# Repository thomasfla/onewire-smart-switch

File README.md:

# onewire-smart-switch
Control and monitor any home lighting setup : a low cost 1-Wire module hidden in your walls.
Adapt to your existing switches, even to 3 and 4ways.

Open source and open hardware.

# details 
A full description of this module is available here:
https://hackaday.io/project/19893-low-cost-smart-switch

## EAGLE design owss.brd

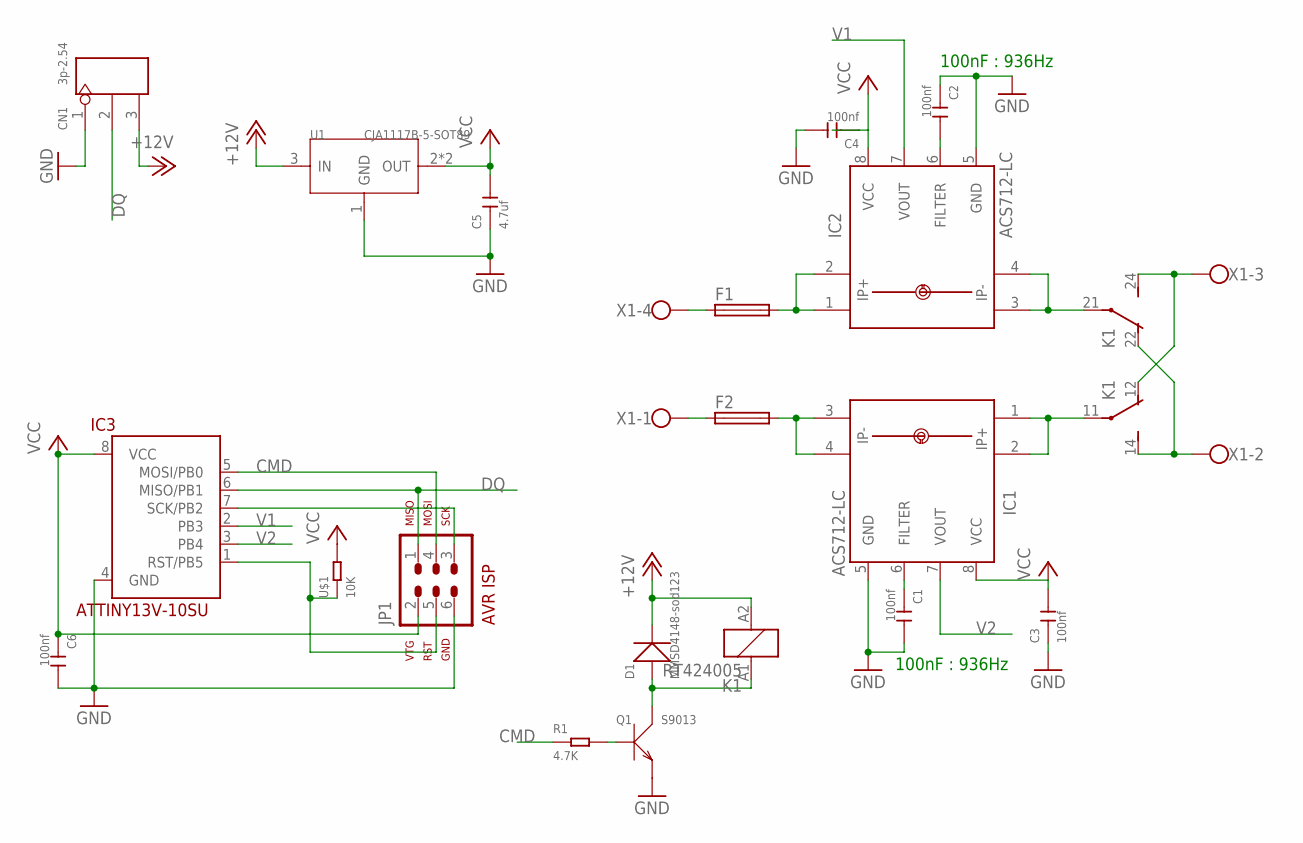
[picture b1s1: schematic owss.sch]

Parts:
C1, C2, C3, C4, C6: 100nf; C0805
C5: 4.7uf; C0805
CN1: 3p-2.54; H3-2.54
D1: MMSD4148-sod123; SOD-123
F1, F2: TE5
IC1, IC2: ACS712-LC; SOIC8
IC3: ATTINY13V-10SU; SOIC8
JP1: AVR-ISP-6
K1: RT424005; RT2C/O
Q1: S9013; SOT-23
R1: 4.7K; R0805
U1: CJA1117B-5-SOT89; SOT-89
U$1: 10K; R0805
X1: W237-4

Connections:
+12V: CN1.3, D1.-, K1.A2 (2), U1.3 (IN)
CMD: IC3.5 (MOSI/PB0), JP1.4, R1.1
DQ: CN1.2, IC3.6 (MISO/PB1), JP1.1
GND: C1.2, C2.1, C3.1, C4.2, C5.1, C6.2, CN1.1, IC1.5 (GND), IC2.5 (GND), IC3.4 (GND), JP1.6, Q1.2 (E), U1.1 (GND)
unnamed: IC1.1 (IP+), IC1.2 (IP+1), K1.11
unnamed: F1.2, IC2.1 (IP+), IC2.2 (IP+1)
unnamed: F1.1, X1.4
unnamed: F2.2, IC1.3 (IP-), IC1.4 (IP-1)
unnamed: K1.12 (O), K1.24 (S), X1.3
unnamed: F2.1, X1.1
unnamed: IC2.3 (IP-), IC2.4 (IP-1), K1.21
unnamed: C1.1, IC1.6 (FILTER)
unnamed: D1.+, K1.A1 (1), Q1.3 (C)
unnamed: C2.2, IC2.6 (FILTER)
unnamed: K1.14 (S), K1.22 (O), X1.2
unnamed: Q1.1 (B), R1.2
unnamed: IC3.7 (SCK/PB2), JP1.3
unnamed: IC3.1 (RST/PB5), JP1.5, U$1.1
V1: IC2.7 (VOUT), IC3.2 (PB3)
V2: IC1.7 (VOUT), IC3.3 (PB4)
VCC: C3.2, C4.1, C5.2, C6.1, IC1.8 (VCC), IC2.8 (VCC), IC3.8 (VCC), JP1.2, U1.2 (OUT), U1.4 (OUT), U$1.2

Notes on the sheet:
100nF : 936Hz

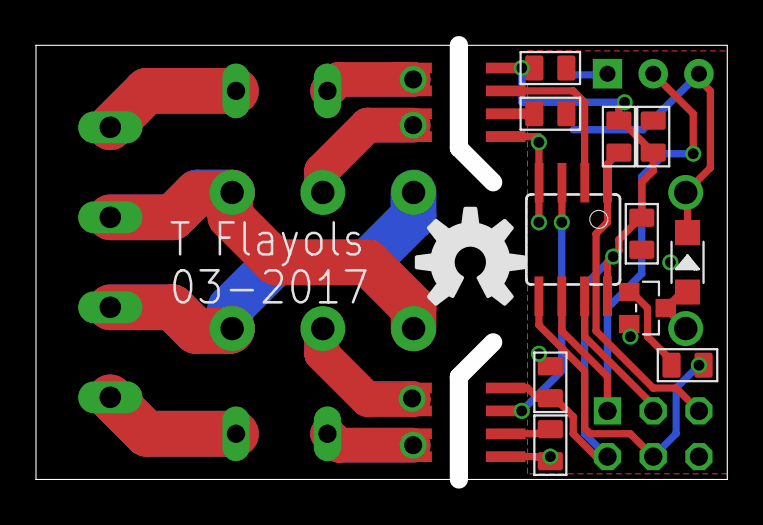
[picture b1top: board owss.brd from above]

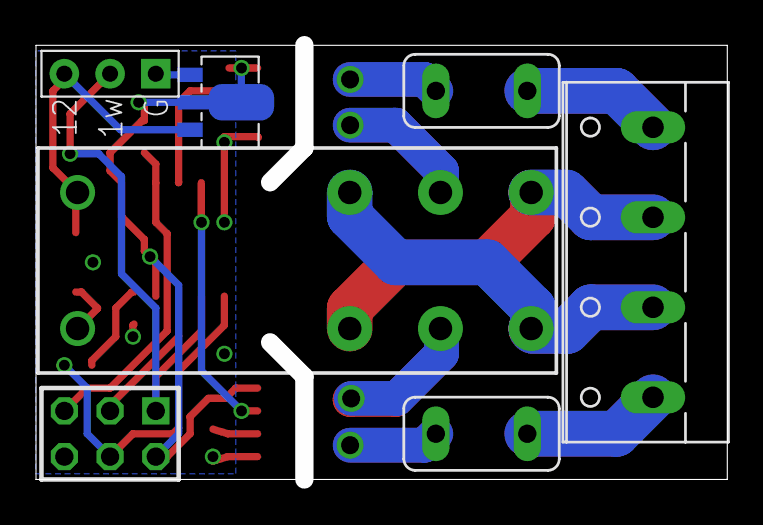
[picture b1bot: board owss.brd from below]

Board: 2 copper layers, 37.4 x 24.1 mm, 20 parts (7 on the bottom side), 21 nets.

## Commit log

2017-03-06 add initial file
2017-03-06 add OSHW logo; make board panelizable
2017-05-03 mv files to PCB
